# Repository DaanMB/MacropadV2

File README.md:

# MacropadV2
A completely rebuilt version of my Macropad project

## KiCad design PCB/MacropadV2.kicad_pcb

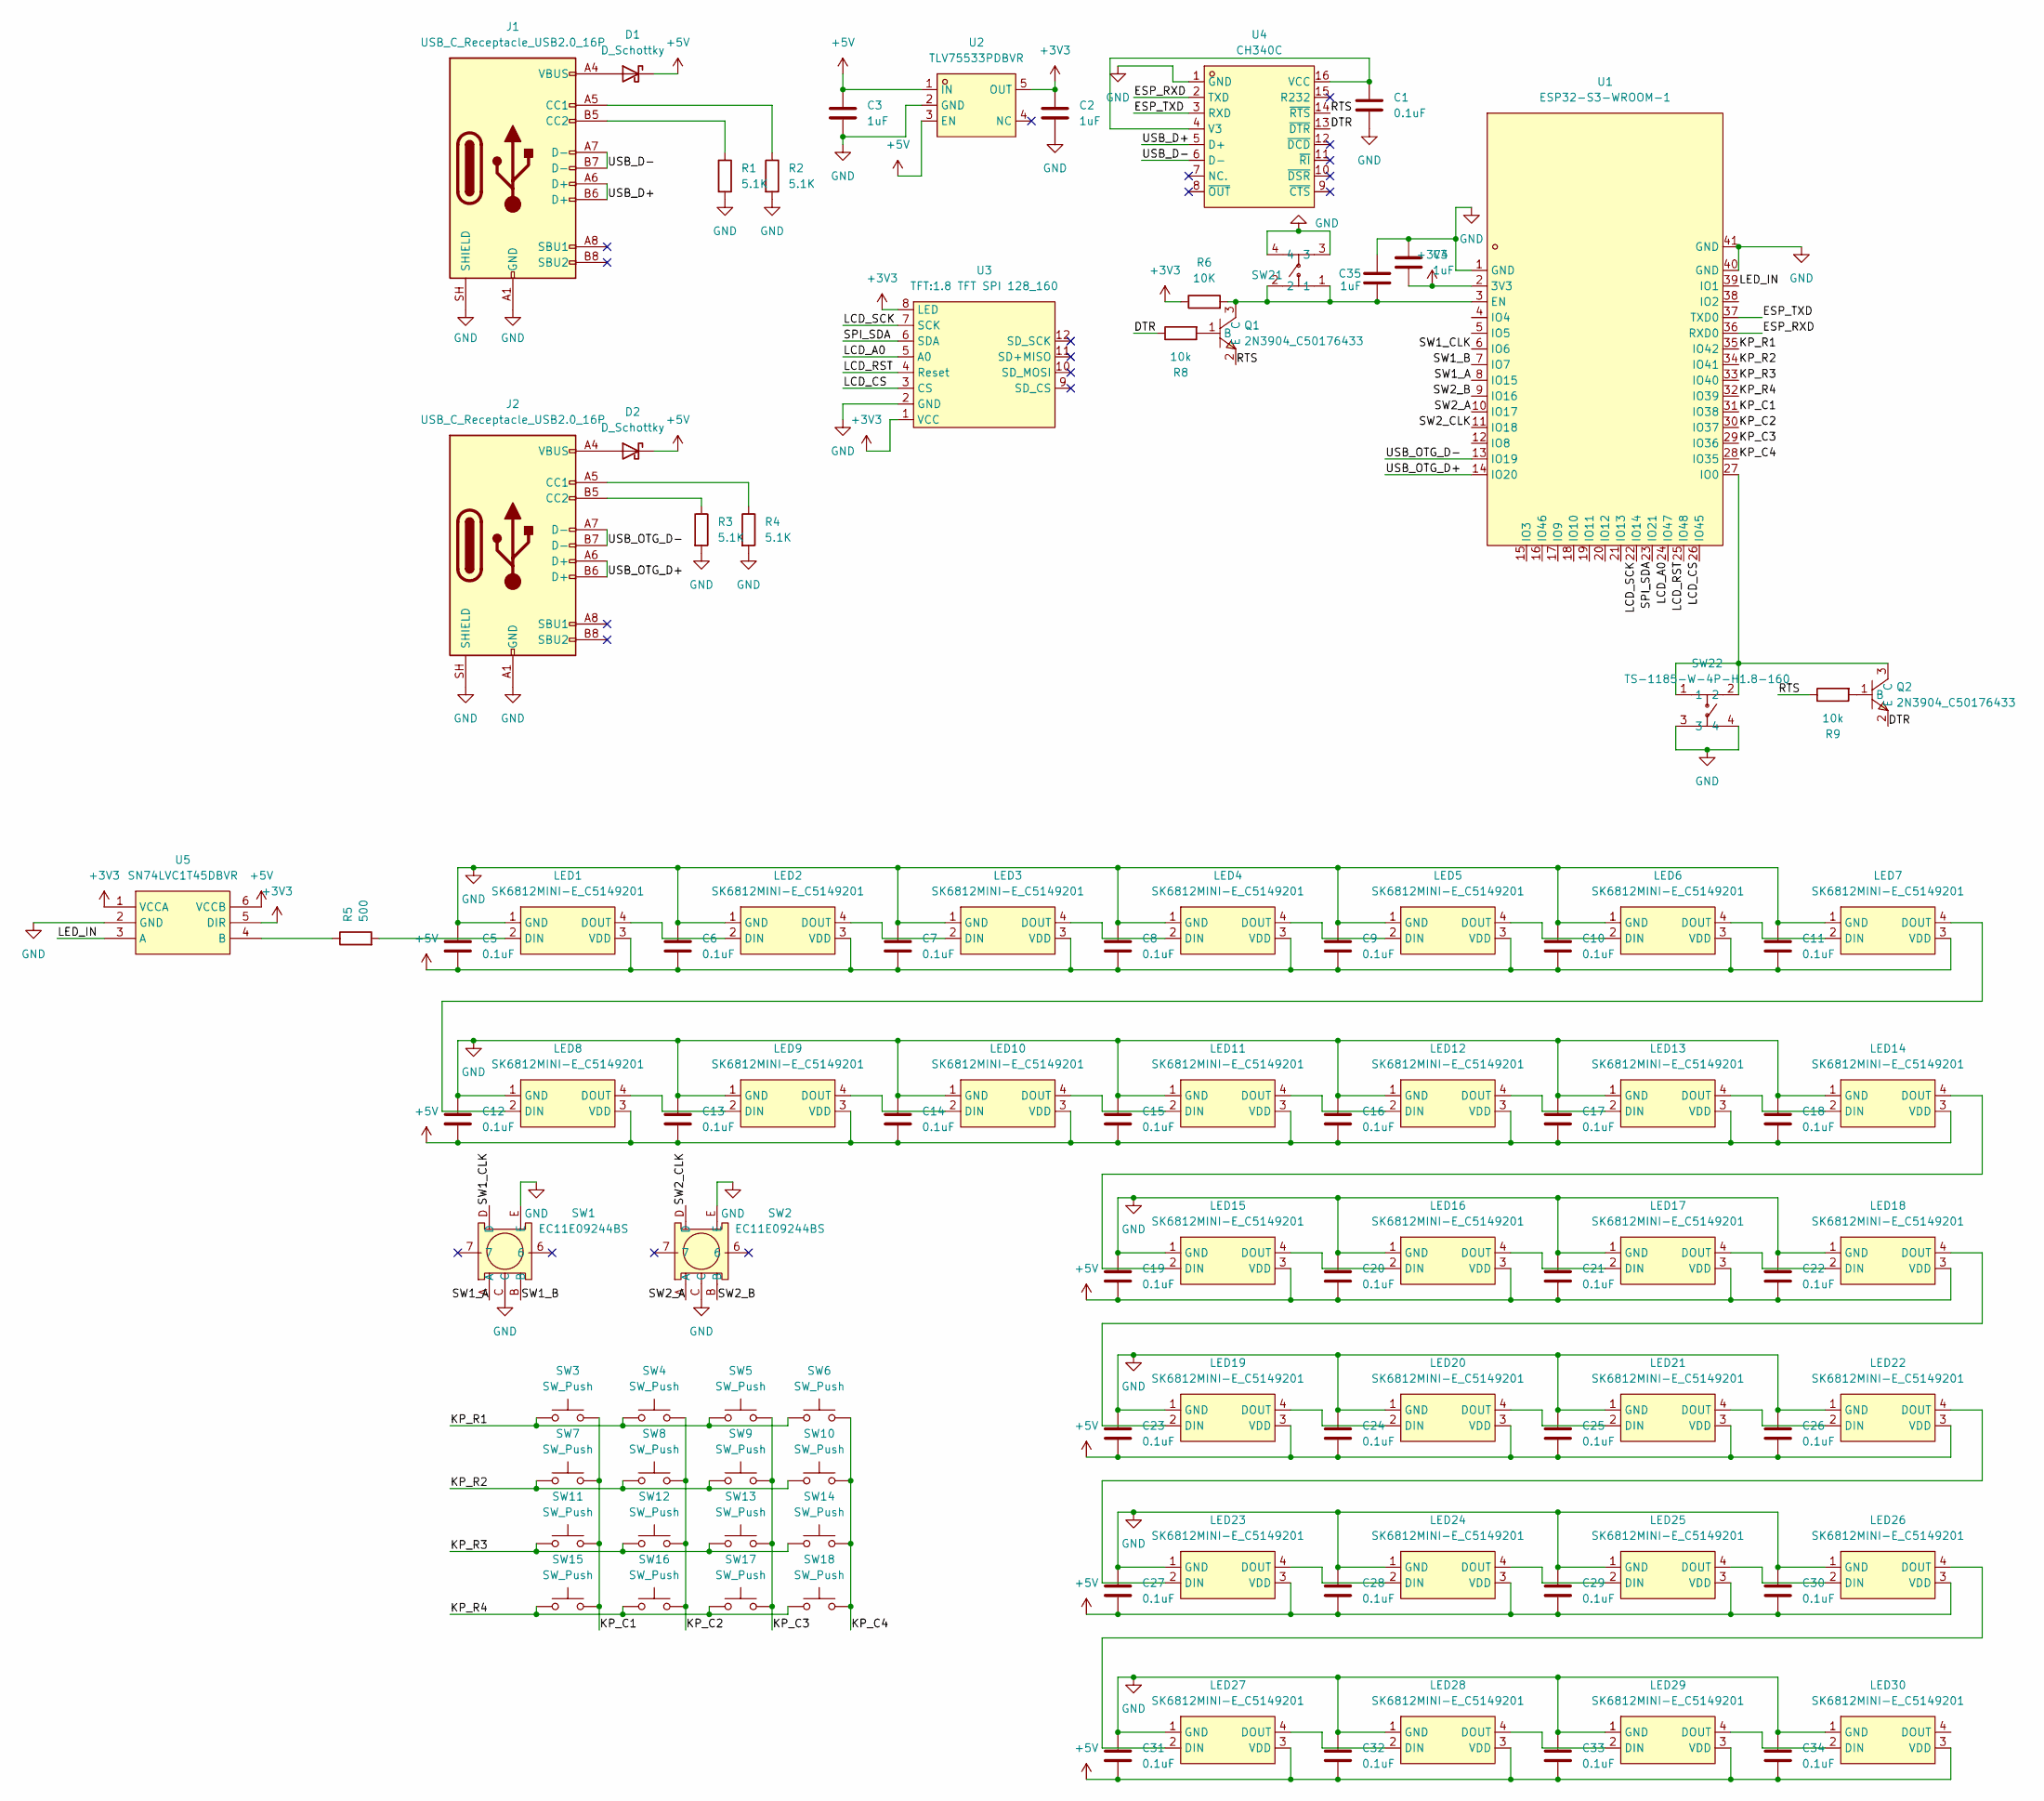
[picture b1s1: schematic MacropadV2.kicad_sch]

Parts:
C1, C5, C6, C7, C8, C9, C10, C11, C12, C13, C14, C15, C16, C17, C18, C19, C20, C21, C22, C23, C24, C25, C26, C27, C28, C29, C30, C31, C32, C33, C34: 0.1uF; C_0603_1608Metric
C2, C3, C4, C35: 1uF; C_0603_1608Metric
D1, D2: D_Schottky; DO-214AC_L4.3-W3.6-LS5.3-RD
J1, J2: USB_C_Receptacle_USB2.0_16P; USB-C-SMD_TYPE-C-16PIN-2MD-073
LED1, LED2, LED3, LED4, LED5, LED6, LED7, LED8, LED9, LED10, LED11, LED12, LED13, LED14, LED15, LED16, LED17, LED18, LED19, LED20, LED21, LED22, LED23, LED24, LED25, LED26, LED27, LED28, LED29, LED30: SK6812MINI-E_C5149201; SK6812MINI-E_fixed; MPN SK6812MINI-E; LCSC Part C5149201
Q1, Q2: 2N3904_C50176433; SOT-23-3_L2.9-W1.3-P1.90-LS2.4-BR; MPN 2N3904; LCSC Part C50176433
R1, R2, R3, R4: 5.1K; R_0603_1608Metric
R5: 500; R_0603_1608Metric
R6: 10K; R_0603_1608Metric
R8, R9: 10k; R_0603_1608Metric
SW1, SW2: EC11E09244BS; SW-TH_EC11XXXXXXXX; MPN EC11E09244BS; LCSC Part C470742
SW3, SW4, SW5, SW6, SW7, SW8, SW9, SW10, SW11, SW12, SW13, SW14, SW15, SW16, SW17, SW18: SW_Push; SW_Cherry_MX_1.00u_PCB
SW21, SW22: TS-1185-W-4P-H1.8-160; SW-SMD_4P-L3.5-W3.0-P1.50-LS4.7; MPN TS-1185-W-4P-H1.8-160; LCSC Part C51927445
U1: ESP32-S3-WROOM-1; WIRELM-SMD_ESP32-S3-WROOM-1; MPN ESP32-S3-WROOM-1-N16R8; LCSC Part C2913202
U2: TLV75533PDBVR; SOT-23-5_L3.0-W1.7-P0.95-LS2.8-BR; MPN TLV75533PDBVR; LCSC Part C404027
U3: 1.8 TFT SPI 128_160
U4: CH340C; SOP-16_L10.0-W3.9-P1.27-LS6.0-BL; MPN CH340C; LCSC Part C84681
U5: SN74LVC1T45DBVR; SOT-23-6_L2.9-W1.6-P0.95-LS2.8-BR; MPN SN74LVC1T45DBVR; LCSC Part C7843

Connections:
+3V3: C2.1, C4.2, R6.1, U1.2 (3V3), U2.5 (OUT), U3.1 (VCC), U3.8 (LED), U5.1 (VCCA), U5.5 (DIR)
+5V: C3.1, C5.2, C6.2, C7.2, C8.2, C9.2, C10.2, C11.2, C12.2, C13.2, C14.2, C15.2, C16.2, C17.2, C18.2, C19.2, C20.2, C21.2, C22.2, C23.2, C24.2, C25.2, C26.2, C27.2, C28.2, C29.2, C30.2, C31.2, C32.2, C33.2, C34.2, D1.1 (K), D2.1 (K), LED1.3 (VDD), LED2.3 (VDD), LED3.3 (VDD), LED4.3 (VDD), LED5.3 (VDD), LED6.3 (VDD), LED7.3 (VDD), LED8.3 (VDD), LED9.3 (VDD), LED10.3 (VDD), LED11.3 (VDD), LED12.3 (VDD), LED13.3 (VDD), LED14.3 (VDD), LED15.3 (VDD), LED16.3 (VDD), LED17.3 (VDD), LED18.3 (VDD), LED19.3 (VDD), LED20.3 (VDD), LED21.3 (VDD), LED22.3 (VDD), LED23.3 (VDD), LED24.3 (VDD), LED25.3 (VDD), LED26.3 (VDD), LED27.3 (VDD), LED28.3 (VDD), LED29.3 (VDD), LED30.3 (VDD), U2.1 (IN), U2.3 (EN), U5.6 (VCCB)
/DTR: Q2.2 (E), R8.1, U4.13 (~DTR)
/ESP_RXD: U1.36 (RXD0), U4.2 (TXD)
/ESP_TXD: U1.37 (TXD0), U4.3 (RXD)
/KP_C1: SW3.2, SW7.2, SW11.2, SW15.2, U1.31 (IO38)
/KP_C2: SW4.2, SW8.2, SW12.2, SW16.2, U1.30 (IO37)
/KP_C3: SW5.2, SW9.2, SW13.2, SW17.2, U1.29 (IO36)
/KP_C4: SW6.2, SW10.2, SW14.2, SW18.2, U1.28 (IO35)
/KP_R1: SW3.1, SW4.1, SW5.1, SW6.1, U1.35 (IO42)
/KP_R2: SW7.1, SW8.1, SW9.1, SW10.1, U1.34 (IO41)
/KP_R3: SW11.1, SW12.1, SW13.1, SW14.1, U1.33 (IO40)
/KP_R4: SW15.1, SW16.1, SW17.1, SW18.1, U1.32 (IO39)
/LCD_A0: U1.24 (IO47), U3.5 (A0)
/LCD_CS: U1.26 (IO45), U3.3 (CS)
/LCD_RST: U1.25 (IO48), U3.4 (Reset)
/LCD_SCK: U1.22 (IO14), U3.7 (SCK)
/LED_IN: U1.39 (IO1), U5.3 (A)
/RTS: Q1.2 (E), R9.1, U4.14 (~RTS)
/SPI_SDA: U1.23 (IO21), U3.6 (SDA)
/SW1_A: SW1.A, U1.8 (IO15)
/SW1_B: SW1.B, U1.7 (IO7)
/SW1_CLK: SW1.D, U1.6 (IO6)
/SW2_A: SW2.A, U1.10 (IO17)
/SW2_B: SW2.B, U1.9 (IO16)
/SW2_CLK: SW2.D, U1.11 (IO18)
/USB_D+: J1.A6 (D+), J1.B6 (D+), U4.5 (D+)
/USB_D-: J1.A7 (D-), J1.B7 (D-), U4.6 (D-)
/USB_OTG_D+: J2.A6 (D+), J2.B6 (D+), U1.14 (IO20)
/USB_OTG_D-: J2.A7 (D-), J2.B7 (D-), U1.13 (IO19)
GND: C1.2, C2.2, C3.2, C4.1, C5.1, C6.1, C7.1, C8.1, C9.1, C10.1, C11.1, C12.1, C13.1, C14.1, C15.1, C16.1, C17.1, C18.1, C19.1, C20.1, C21.1, C22.1, C23.1, C24.1, C25.1, C26.1, C27.1, C28.1, C29.1, C30.1, C31.1, C32.1, C33.1, C34.1, C35.1, J1.A1 (GND), J1.A12 (GND), J1.B1 (GND), J1.B12 (GND), J1.SH (SHIELD), J2.A1 (GND), J2.A12 (GND), J2.B1 (GND), J2.B12 (GND), J2.SH (SHIELD), LED1.1 (GND), LED2.1 (GND), LED3.1 (GND), LED4.1 (GND), LED5.1 (GND), LED6.1 (GND), LED7.1 (GND), LED8.1 (GND), LED9.1 (GND), LED10.1 (GND), LED11.1 (GND), LED12.1 (GND), LED13.1 (GND), LED14.1 (GND), LED15.1 (GND), LED16.1 (GND), LED17.1 (GND), LED18.1 (GND), LED19.1 (GND), LED20.1 (GND), LED21.1 (GND), LED22.1 (GND), LED23.1 (GND), LED24.1 (GND), LED25.1 (GND), LED26.1 (GND), LED27.1 (GND), LED28.1 (GND), LED29.1 (GND), LED30.1 (GND), R1.2, R2.2, R3.2, R4.2, SW1.C, SW1.E, SW2.C, SW2.E, SW21.3, SW21.4, SW22.3, SW22.4, U1.1 (GND), U1.40 (GND), U1.41 (GND), U2.2 (GND), U3.2 (GND), U4.1 (GND), U5.2 (GND)
unnamed: D1.2 (A), J1.A4 (VBUS), J1.A9 (VBUS), J1.B4 (VBUS), J1.B9 (VBUS)
unnamed: D2.2 (A), J2.A4 (VBUS), J2.A9 (VBUS), J2.B4 (VBUS), J2.B9 (VBUS)
unnamed: J1.A5 (CC1), R2.1
unnamed: J1.B5 (CC2), R1.1
unnamed: J2.A5 (CC1), R4.1
unnamed: J2.B5 (CC2), R3.1
unnamed: LED1.2 (DIN), R5.2
unnamed: LED1.4 (DOUT), LED2.2 (DIN)
unnamed: LED2.4 (DOUT), LED3.2 (DIN)
unnamed: LED3.4 (DOUT), LED4.2 (DIN)
unnamed: LED4.4 (DOUT), LED5.2 (DIN)
unnamed: LED5.4 (DOUT), LED6.2 (DIN)
unnamed: LED6.4 (DOUT), LED7.2 (DIN)
unnamed: LED7.4 (DOUT), LED8.2 (DIN)
unnamed: LED8.4 (DOUT), LED9.2 (DIN)
unnamed: LED9.4 (DOUT), LED10.2 (DIN)
unnamed: LED10.4 (DOUT), LED11.2 (DIN)
unnamed: LED11.4 (DOUT), LED12.2 (DIN)
unnamed: LED12.4 (DOUT), LED13.2 (DIN)
unnamed: LED13.4 (DOUT), LED14.2 (DIN)
unnamed: LED14.4 (DOUT), LED15.2 (DIN)
unnamed: LED15.4 (DOUT), LED16.2 (DIN)
unnamed: LED16.4 (DOUT), LED17.2 (DIN)
unnamed: LED17.4 (DOUT), LED18.2 (DIN)
unnamed: LED18.4 (DOUT), LED19.2 (DIN)
unnamed: LED19.4 (DOUT), LED20.2 (DIN)
unnamed: LED20.4 (DOUT), LED21.2 (DIN)
unnamed: LED21.4 (DOUT), LED22.2 (DIN)
unnamed: LED22.4 (DOUT), LED23.2 (DIN)
unnamed: LED23.4 (DOUT), LED24.2 (DIN)
unnamed: LED24.4 (DOUT), LED25.2 (DIN)
unnamed: LED25.4 (DOUT), LED26.2 (DIN)
unnamed: LED26.4 (DOUT), LED27.2 (DIN)
unnamed: LED27.4 (DOUT), LED28.2 (DIN)
unnamed: LED28.4 (DOUT), LED29.2 (DIN)
unnamed: LED29.4 (DOUT), LED30.2 (DIN)
unnamed: Q1.1 (B), R8.2
unnamed: C35.2, Q1.3 (C), R6.2, SW21.1, SW21.2, U1.3 (EN)
unnamed: Q2.1 (B), R9.2
unnamed: Q2.3 (C), SW22.1, SW22.2, U1.27 (IO0)
unnamed: C1.1, U4.4 (V3), U4.16 (VCC)
unnamed: R5.1, U5.4 (B)

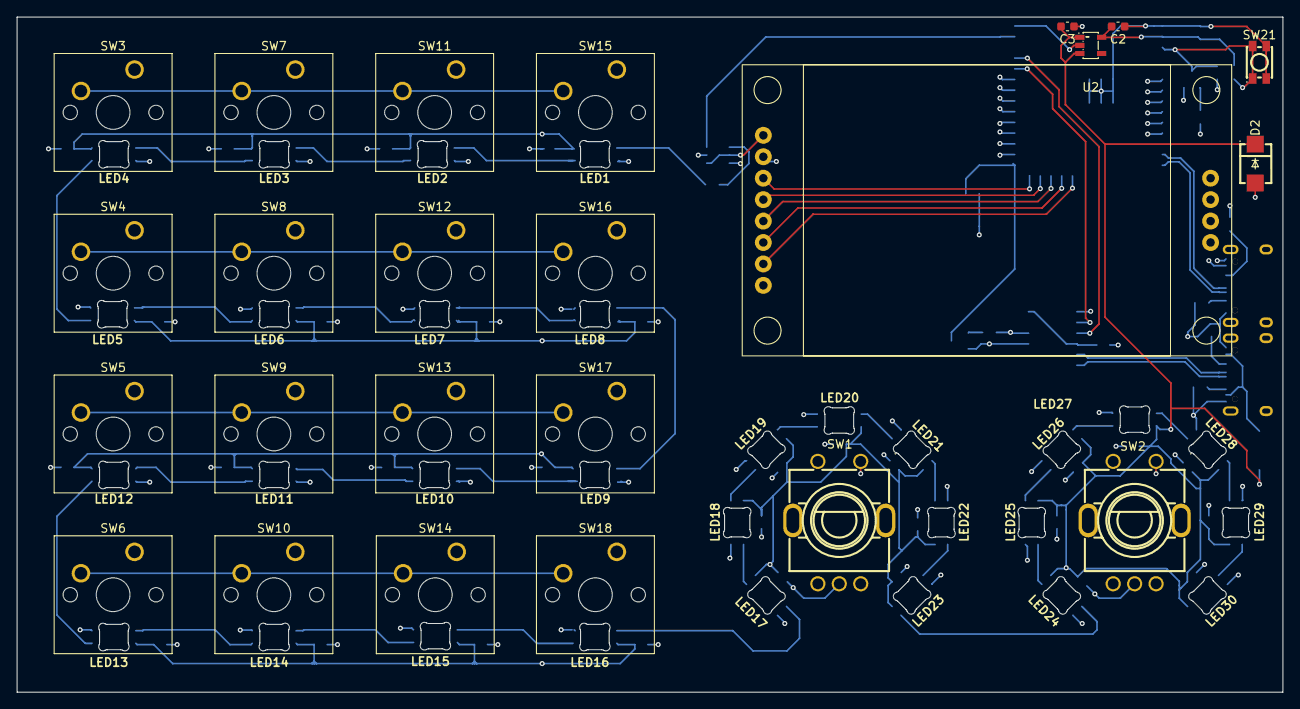
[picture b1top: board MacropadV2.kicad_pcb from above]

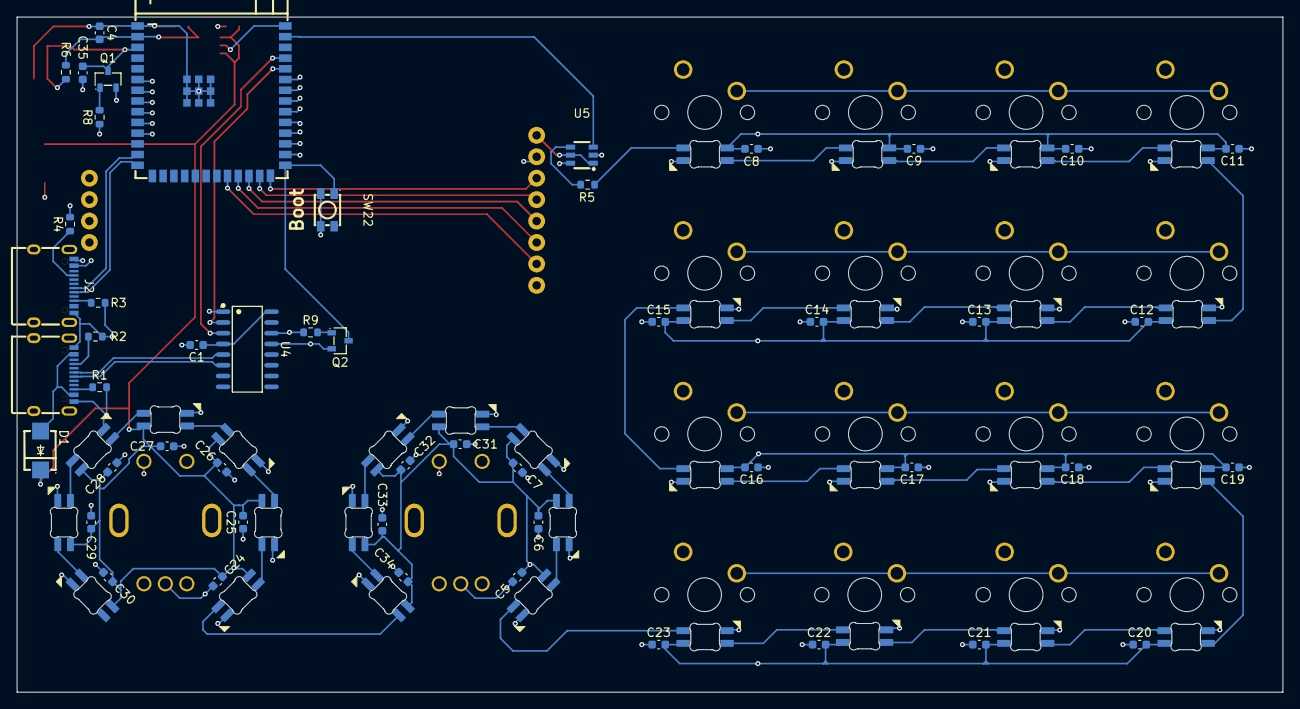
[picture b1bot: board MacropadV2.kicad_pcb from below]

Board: 4 copper layers, 150.0 x 80.0 mm, 104 parts (50 on the bottom side), 73 nets.
